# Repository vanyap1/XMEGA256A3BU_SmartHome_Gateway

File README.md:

# XMEGA256A3BU_SmartHome_Gateway

## Опис проекту
Це шлюз для розумного будинку, який може з'єднувати різні типи пристроїв з різними інтерфейсами, передавати та буферизувати між ними інформацію, реалізувати власну логіку та багато іншого.

## Можливості
- Підтримка інтерфейсів: LAN, CAN, SPI, I2C, GPIO
- Релейні виходи та входи з оптичною розв'язкою
- SD карта для логів
- Веб сервер для керування

## Структура проекту
- **XMEGA_A3BU**: Основний код проекту
  - `main.c`: Головний файл програми
  - `driver/`: Драйвери для різних периферійних пристроїв
  - `libs/`: Бібліотеки для роботи з різними інтерфейсами та пристроями
- **eagle_src**: Схеми та плати проекту
  - `controller_V1.brd`: Файл плати
  - `controller_V1.sch`: Схема проекту

## Контролер
В проекті використовується контролер **XMEGA256A3BU**. Основні переваги цього контролера:
- Висока продуктивність завдяки 8/16-бітному процесору
- Велика кількість периферійних інтерфейсів
- Низьке енергоспоживання
- Вбудована підтримка USB

## Фото модуля

## Інструкції по збірці
Для збірки проекту використовуйте Makefile, який знаходиться у директорії `XMEGA_A3BU/Debug/`.

```sh
cd XMEGA_A3BU/Debug/
make

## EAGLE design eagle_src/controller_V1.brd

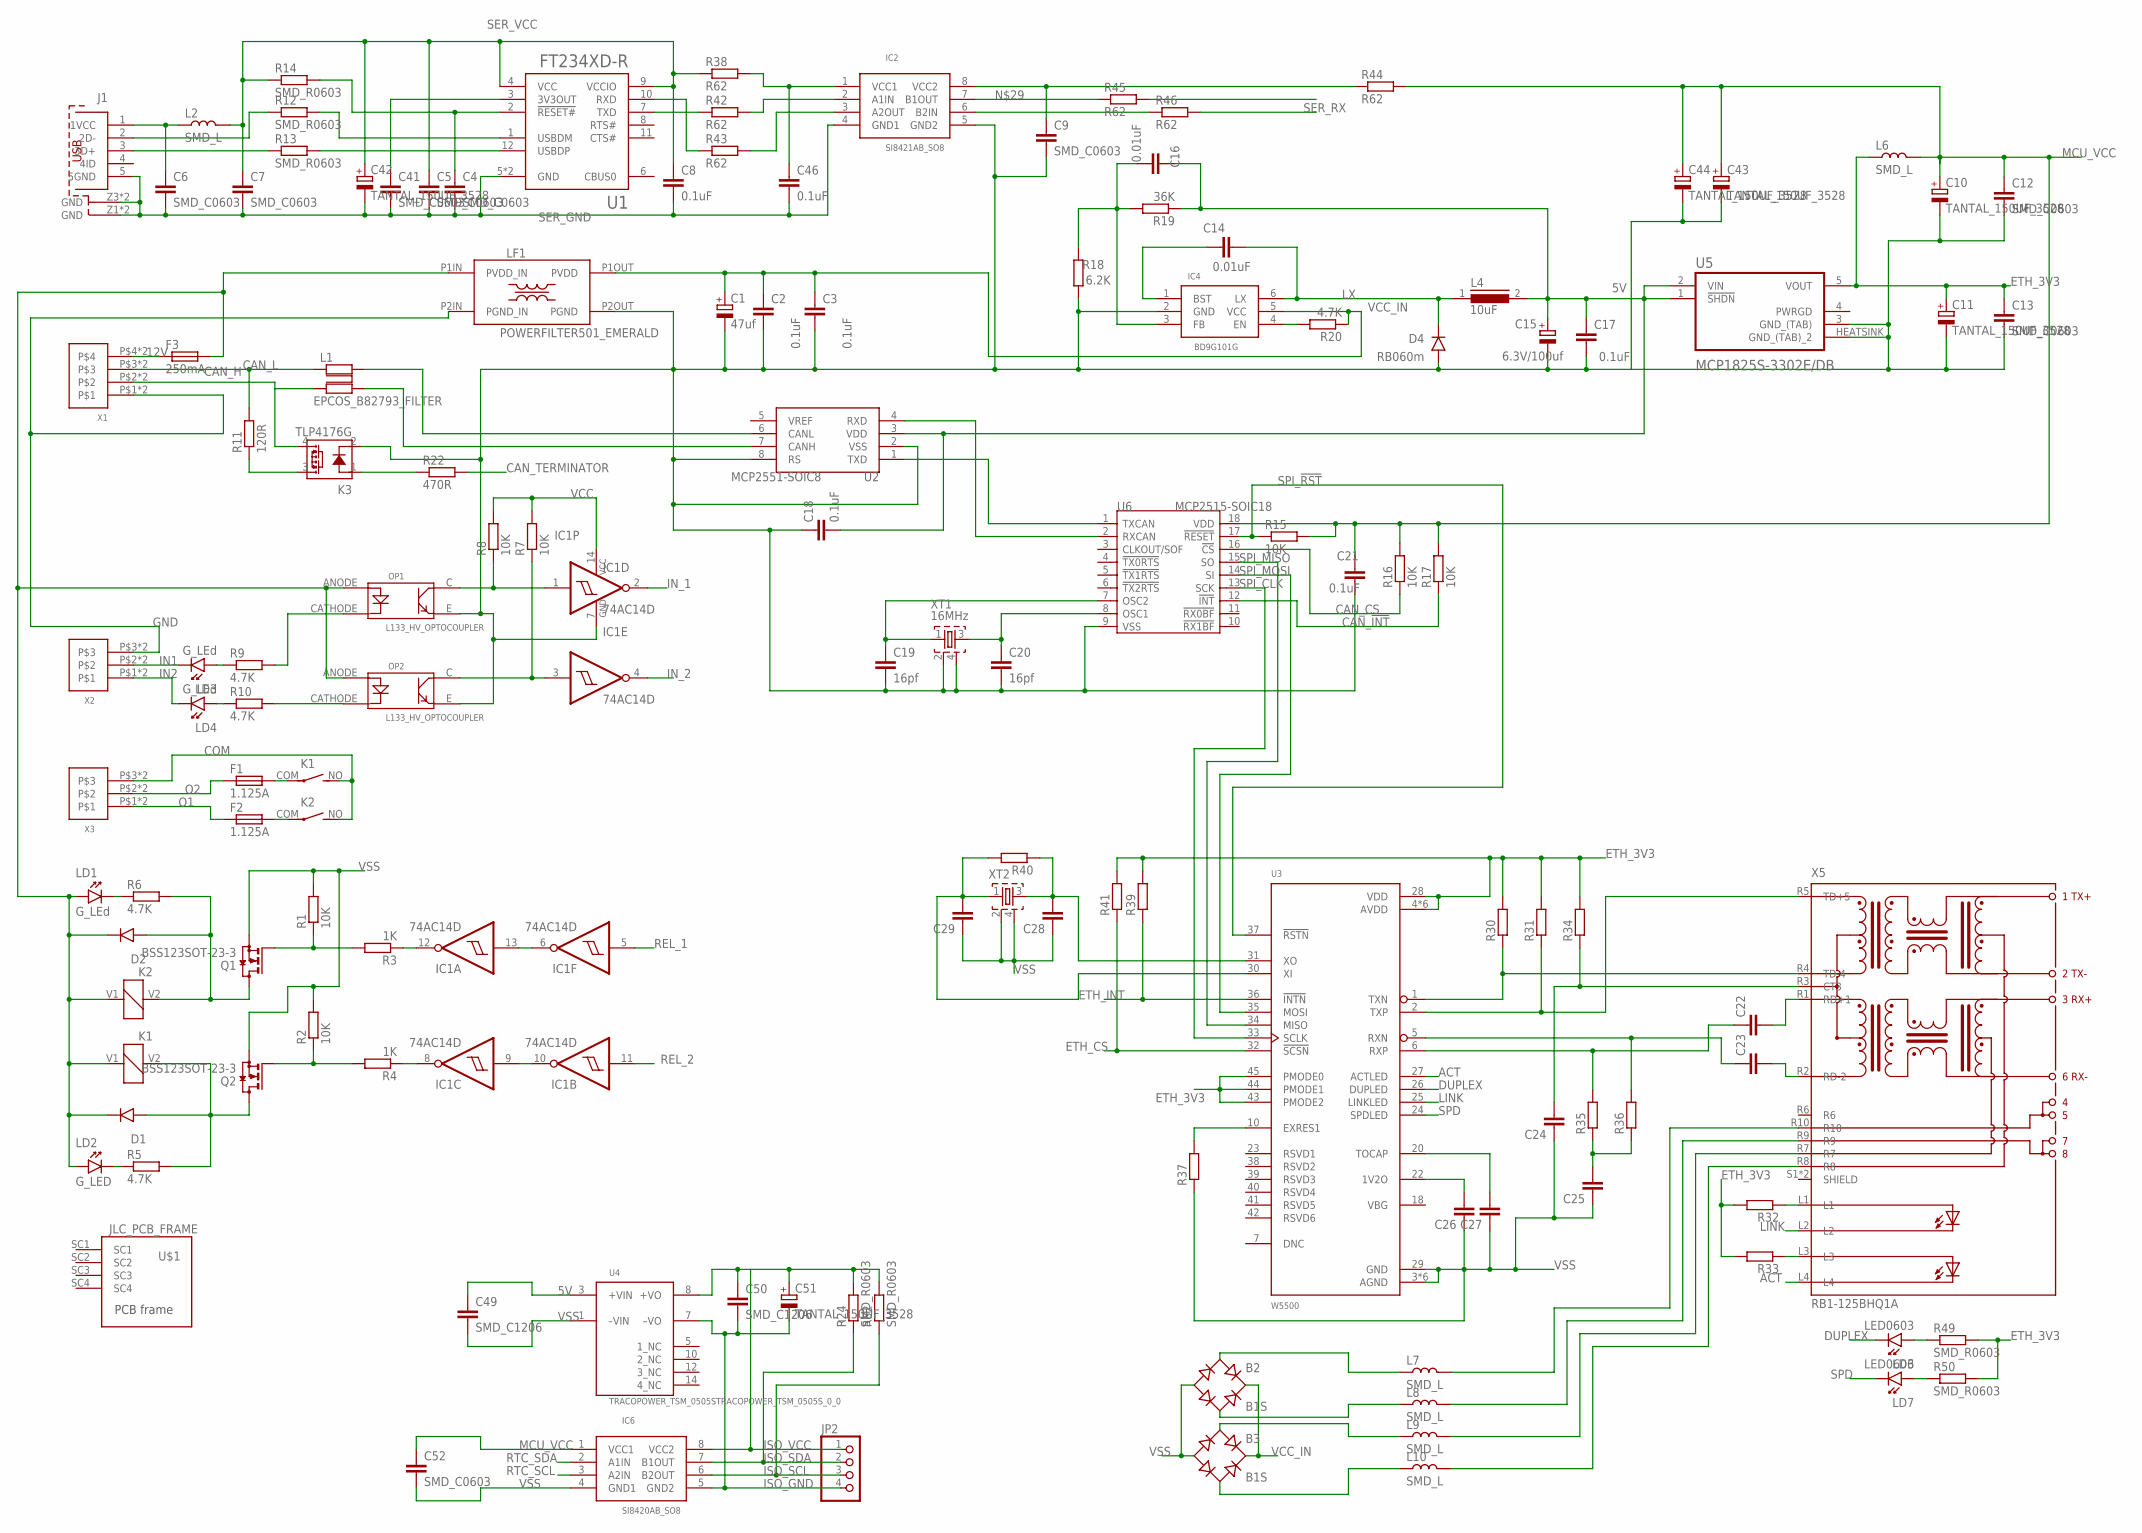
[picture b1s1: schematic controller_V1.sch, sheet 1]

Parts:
B2, B3: B1S; MBS
C1: 47uf; 5.08MM
C2, C3: 0.1uF; 1206
C4, C5, C6, C7, C9, C12, C13, C22, C23, C26, C27, C28, C29, C41, C52: SMD_C0603; 0603
C8, C17, C18, C21, C46: 0.1uF; 0603
C10, C11, C42, C43, C44, C51: TANTAL_150UF_3528; KA-3528ASYC
C14, C16: 0.01uF; 0603
C15: 6.3V/100uf; D/7343-31R
C19, C20: 16pf; 0603
C24: 0.1uf; 0603
C25: 10nf; 0603
C49, C50: SMD_C1206; 1206
D1, D2: D_MBRA340G; SMA403D
D4: RB060m; SMA403D
F1, F2: 1.125A; FUSE_DIP_2.5A250V
F3: 250mA; SMD_2410_FUSE_NOK
IC1: 74AC14D; SO14
IC2: SI8421AB_SO8; SO8
IC4: BD9G101G; SOT-23(6)
IC6: SI8420AB_SO8; SO8
J1: MINI_USB_TYP_B_@; 65100516121
JP2: PINHD-1X4; 1X04
K1, K2: 12-H1(610); 12-H1(610)_DIP
K3: TLP4176G; SOP04
L1: EPCOS_B82793_FILTER; EPCOS_FILTER
L2, L6, L7, L8, L9, L10: SMD_L; 0805
L4: 10uF; DR74
LD1, LD3, LD4: G_LEd; 3MM_DIP_LED
LD2: G_LED; 3MM_DIP_LED
LD6, LD7: LED0603; 0603_P
LF1: POWERFILTER501_EMERALD; POWERFILTER
OP1, OP2: L133_HV_OPTOCOUPLER; HV_OPTOCOUPLER_L133
Q1, Q2: BSS123SOT-23-3; SOT-23(3)
R1, R2, R7, R8, R15, R16, R17: 10K; 0603
R3, R4: 1K; 0603
R5, R6, R9, R10, R20: 4.7K; 0603
R11: 120R; VMTA55
R12, R13, R14, R24, R30, R31, R32, R33, R34, R35, R36, R37, R39, R40, R41, R49, R50, R52: SMD_R0603; 0603
R18: 6.2K; 0603
R19: 36K; 0603
R22: 470R; 0603
R38, R42, R43, R44, R45, R46: R62; 0603
U1: FT234XD-R; IC_FT234XD-R
U2: MCP2551-SOIC8; SO8
U3: W5500; QFP50P900X900X160-48N
U4: TRACOPOWER_TSM_0505STRACOPOWER_TSM_0505S_0_0; TRACOPOWER_TSM_0505S_0
U5: MCP1825S-3302E/DB; SOT230P700X180-4N
U6: MCP2515-SOIC18; SO18L
U$1: JLC_PCB_FRAME; 80X100_PCB_FRAME
X1: WAGO250_X4; WAGO250_FP_4X
X2, X3: WAGO250_X3; WAGO250_FP_3X
X5: RB1-125BHQ1A
XT1: 16MHz; QUARTZ_3X3MM
XT2: QUARTZ_ZQ; QUARTZ_3X3MM

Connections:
5V: C15.+, C16.2, C17.2, C18.2, C49.1, L4.2, R19.1, U2.3 (VDD), U4.3 (+VIN), U5.1 (!SHDN), U5.2 (VIN)
12V: F3.P$1 (1), X1.P$4, X1.U$4
ACT: U3.27 (ACTLED), X5.L4
CAN_!INT: R17.1, U6.12 (!INT); also elsewhere on the board
CAN_CS: R16.1, U6.16 (!CS); also elsewhere on the board
CAN_H: K3.4 (DS2), L1.P$2 (2), X1.P$2, X1.U$2
CAN_L: L1.P$1 (1), R11.2, X1.P$3, X1.U$3
CAN_TERMINATOR: R22.2; also elsewhere on the board
COM: K1.NO (S), K2.NO (S), X3.P$3, X3.U$3
DUPLEX: LD6.1 (K), U3.26 (DUPLED)
ETH_3V3: C11.P (+), C13.1, L6.1, R30.2, R31.2, R32.2, R33.2, R34.2, R39.2, R41.2, R49.2, R50.2, U3.4 (AVDD), U3.8 (AVDD), U3.11 (AVDD), U3.15 (AVDD), U3.17 (AVDD), U3.21 (AVDD), U3.28 (VDD), U3.43 (PMODE2), U3.44 (PMODE1), U3.45 (PMODE0), U5.5 (VOUT)
ETH_CS: R41.1, U3.32 (!SCSN); also elsewhere on the board
ETH_INT: R39.1, U3.36 (!INTN); also elsewhere on the board
GND: LF1.P2IN (PGND_IN), X1.P$1, X1.U$1, X2.P$3, X2.U$3
IN1: LD3.K, X2.P$2, X2.U$2
IN2: LD4.K, X2.P$1, X2.U$1
IN_1: IC1.2 (O); also elsewhere on the board
IN_2: IC1.4 (O); also elsewhere on the board
ISO_GND: C50.2, C51.M (-), IC6.5 (GND2), JP2.4, U4.7 (–VO)
ISO_SCL: IC6.6 (B2OUT), JP2.3, R52.1
ISO_SDA: IC6.7 (B1OUT), JP2.2, R24.1
ISO_VCC: C50.1, C51.P (+), IC6.8 (VCC2), JP2.1, R24.2, R52.2, U4.8 (+VO)
LINK: U3.25 (LINKLED), X5.L2
LX: C14.2, D4.P$1 (C), IC4.6 (LX), L4.1
MCU_VCC: C10.P (+), C12.1, C21.1, C43.P (+), C44.P (+), C52.1, IC6.1 (VCC1), L6.2, R15.2, R16.2, R17.2, R44.2, U6.18 (VDD); also elsewhere on the board
unnamed: IC2.3 (A2OUT), R43.2
unnamed: F1.P$2 (2), K1.COM
unnamed: F2.P$2 (2), K2.COM
unnamed: C41.1, U1.3 (3V3OUT)
unnamed: Q2.1 (G), R2.1, R4.2
unnamed: D1.P$2 (A), K1.V2 (2), Q2.3 (D), R5.2
unnamed: D2.P$2 (A), K2.V2 (2), Q1.3 (D), R6.2
unnamed: Q1.1 (G), R1.1, R3.2
unnamed: LD1.K, R6.1
unnamed: LD2.K, R5.1
unnamed: IC2.2 (A1IN), R42.2
unnamed: IC1.9 (I), IC1.10 (O)
unnamed: IC1.8 (O), R4.1
unnamed: IC1.6 (O), IC1.13 (I)
unnamed: IC1.12 (O), R3.1
unnamed: IC1.1 (I), OP1.C (COLLECTOR), R8.1
unnamed: IC1.3 (I), OP2.C (COLLECTOR), R7.1
unnamed: L10.2, X5.R8
unnamed: C46.1, IC2.1 (VCC1), R38.2
unnamed: D1.P$1 (C), D2.P$1 (C), F3.P$2 (2), K1.V1 (1), K2.V1 (1), LD1.A, LD2.A, LF1.P1IN (PVDD_IN), OP1.ANODE (ANOD), OP2.ANODE (ANOD)
unnamed: OP2.CATHODE (CATHOD), R10.2
unnamed: OP1.CATHODE (CATHOD), R9.2
unnamed: LD3.A, R9.1
unnamed: LD4.A, R10.1
unnamed: C9.1, IC2.8 (VCC2), R44.1
unnamed: IC2.7 (B1OUT), R45.1
unnamed: IC2.6 (B2IN), R46.1
unnamed: K3.3 (DS1), R11.1
unnamed: U2.1 (TXD), U6.1 (TXCAN)
unnamed: J1.3 (3D+), R13.1
unnamed: U2.4 (RXD), U6.2 (RXCAN)
unnamed: R13.2, U1.12 (USBDP)
unnamed: R12.2, U1.1 (USBDM)
unnamed: J1.2 (2D-), R12.1
unnamed: C4.1, R14.2, U1.2 (!RESET#)
unnamed: R42.1, U1.7 (TXD)
unnamed: C6.1, J1.1 (1VCC), L2.1
unnamed: L9.2, X5.R7
unnamed: L8.2, X5.R9
unnamed: R43.1, U1.10 (RXD)
unnamed: L1.P$3 (3), U2.7 (CANH)
unnamed: L1.P$4 (4), U2.6 (CANL)
unnamed: C14.1, IC4.1 (BST)
unnamed: L7.2, X5.R10
unnamed: C16.1, IC4.3 (FB), R18.2, R19.2
unnamed: IC4.4 (EN), R20.2
unnamed: C19.1, U6.7 (OSC2), XT1.1
unnamed: K3.1 (A), R22.1
unnamed: C20.1, U6.8 (OSC1), XT1.3
unnamed: B2.AC1, L7.1
unnamed: B2.AC2, L8.1
unnamed: B3.AC1, L9.1
unnamed: B3.AC2, L10.1
unnamed: LD6.2 (A), R49.1
unnamed: LD7.2 (A), R50.1
unnamed: C22.1, R35.2, U3.6 (RXP)
unnamed: C23.1, R36.2, U3.5 (RXN)
unnamed: R30.1, U3.1 (TXN), X5.R4 (TD-4)
unnamed: R31.1, U3.2 (TXP), X5.R5 (TD+5)
unnamed: C24.2, R34.1, X5.R3 (CT3)
unnamed: C25.2, R35.1, R36.1
unnamed: C22.2, X5.R1 (RD+1)
unnamed: C23.2, X5.R2 (RD-2)
unnamed: R32.1, X5.L1
unnamed: R33.1, X5.L3
unnamed: C26.2, U3.22 (1V2O)
unnamed: C27.2, U3.20 (TOCAP)
unnamed: R37.2, U3.10 (EXRES1)
unnamed: C29.2, R40.2, U3.30 (XI), XT2.1
unnamed: C28.2, R40.1, U3.31 (XO), XT2.3
O1: F2.P$1 (1), X3.P$1, X3.U$1
O2: F1.P$1 (1), X3.P$2, X3.U$2
REL_1: IC1.5 (I); also elsewhere on the board
REL_2: IC1.11 (I); also elsewhere on the board
RTC_SCL: IC6.3 (A2IN); also elsewhere on the board
RTC_SDA: IC6.2 (A1IN); also elsewhere on the board
SER_GND: C4.2, C5.2, C6.2, C7.2, C8.2, C41.2, C42.M (-), C46.2, IC2.4 (GND1), J1.5 (5GND), J1.Z1 (GND), J1.Z2 (GND), J1.Z3 (GND), J1.Z4 (GND), U1.5 (GND), U1.13 (GND)
SER_RX: R46.2; also elsewhere on the board
SER_TX: R45.2; also elsewhere on the board
SER_VCC: C5.1, C7.1, C8.1, C42.P (+), L2.2, R14.1, R38.1, U1.4 (VCC), U1.9 (VCCIO)
SPD: LD7.1 (K), U3.24 (SPDLED)
SPI_!RST: R15.1, U3.37 (!RSTN), U6.17 (!RESET); also elsewhere on the board
SPI_CLK: U3.33 (SCLK), U6.13 (SCK); also elsewhere on the board
SPI_MISO: U3.34 (MISO), U6.15 (SO); also elsewhere on the board
SPI_MOSI: U3.35 (MOSI), U6.14 (SI); also elsewhere on the board
VCC: IC1.14 (VCC), R7.2, R8.2; also elsewhere on the board
VCC_IN: B2.+, B3.+, C1.P$2 (+), C2.1, C3.1, IC4.5 (VCC), LF1.P1OUT (PVDD), R20.1
VSS: B2.-, B3.-, C1.P$1 (-), C2.2, C3.2, C9.2, C10.M (-), C11.M (-), C12.2, C13.2, C15.-, C17.1, C18.1, C19.2, C20.2, C21.2, C24.1, C25.1, C26.1, C27.1, C28.1, C29.1, C43.M (-), C44.M (-), C49.2, C52.2, D4.P$2 (A), IC1.7 (GND), IC2.5 (GND2), IC4.2 (GND), IC6.4 (GND1), K3.2 (K), LF1.P2OUT (PGND), OP1.E (EMITTER), OP2.E (EMITTER), Q1.2 (S), Q2.2 (S), R1.2, R2.2, R18.1, R37.1, U2.2 (VSS), U2.8 (RS), U3.3 (AGND), U3.9 (AGND), U3.14 (AGND), U3.16 (AGND), U3.19 (AGND), U3.29 (GND), U3.48 (AGND), U4.1 (–VIN), U5.3 (GND_(TAB)), U5.HEATSINK (GND_(TAB)_2), U6.9 (VSS), XT1.2, XT1.4, XT2.2, XT2.4; also elsewhere on the board

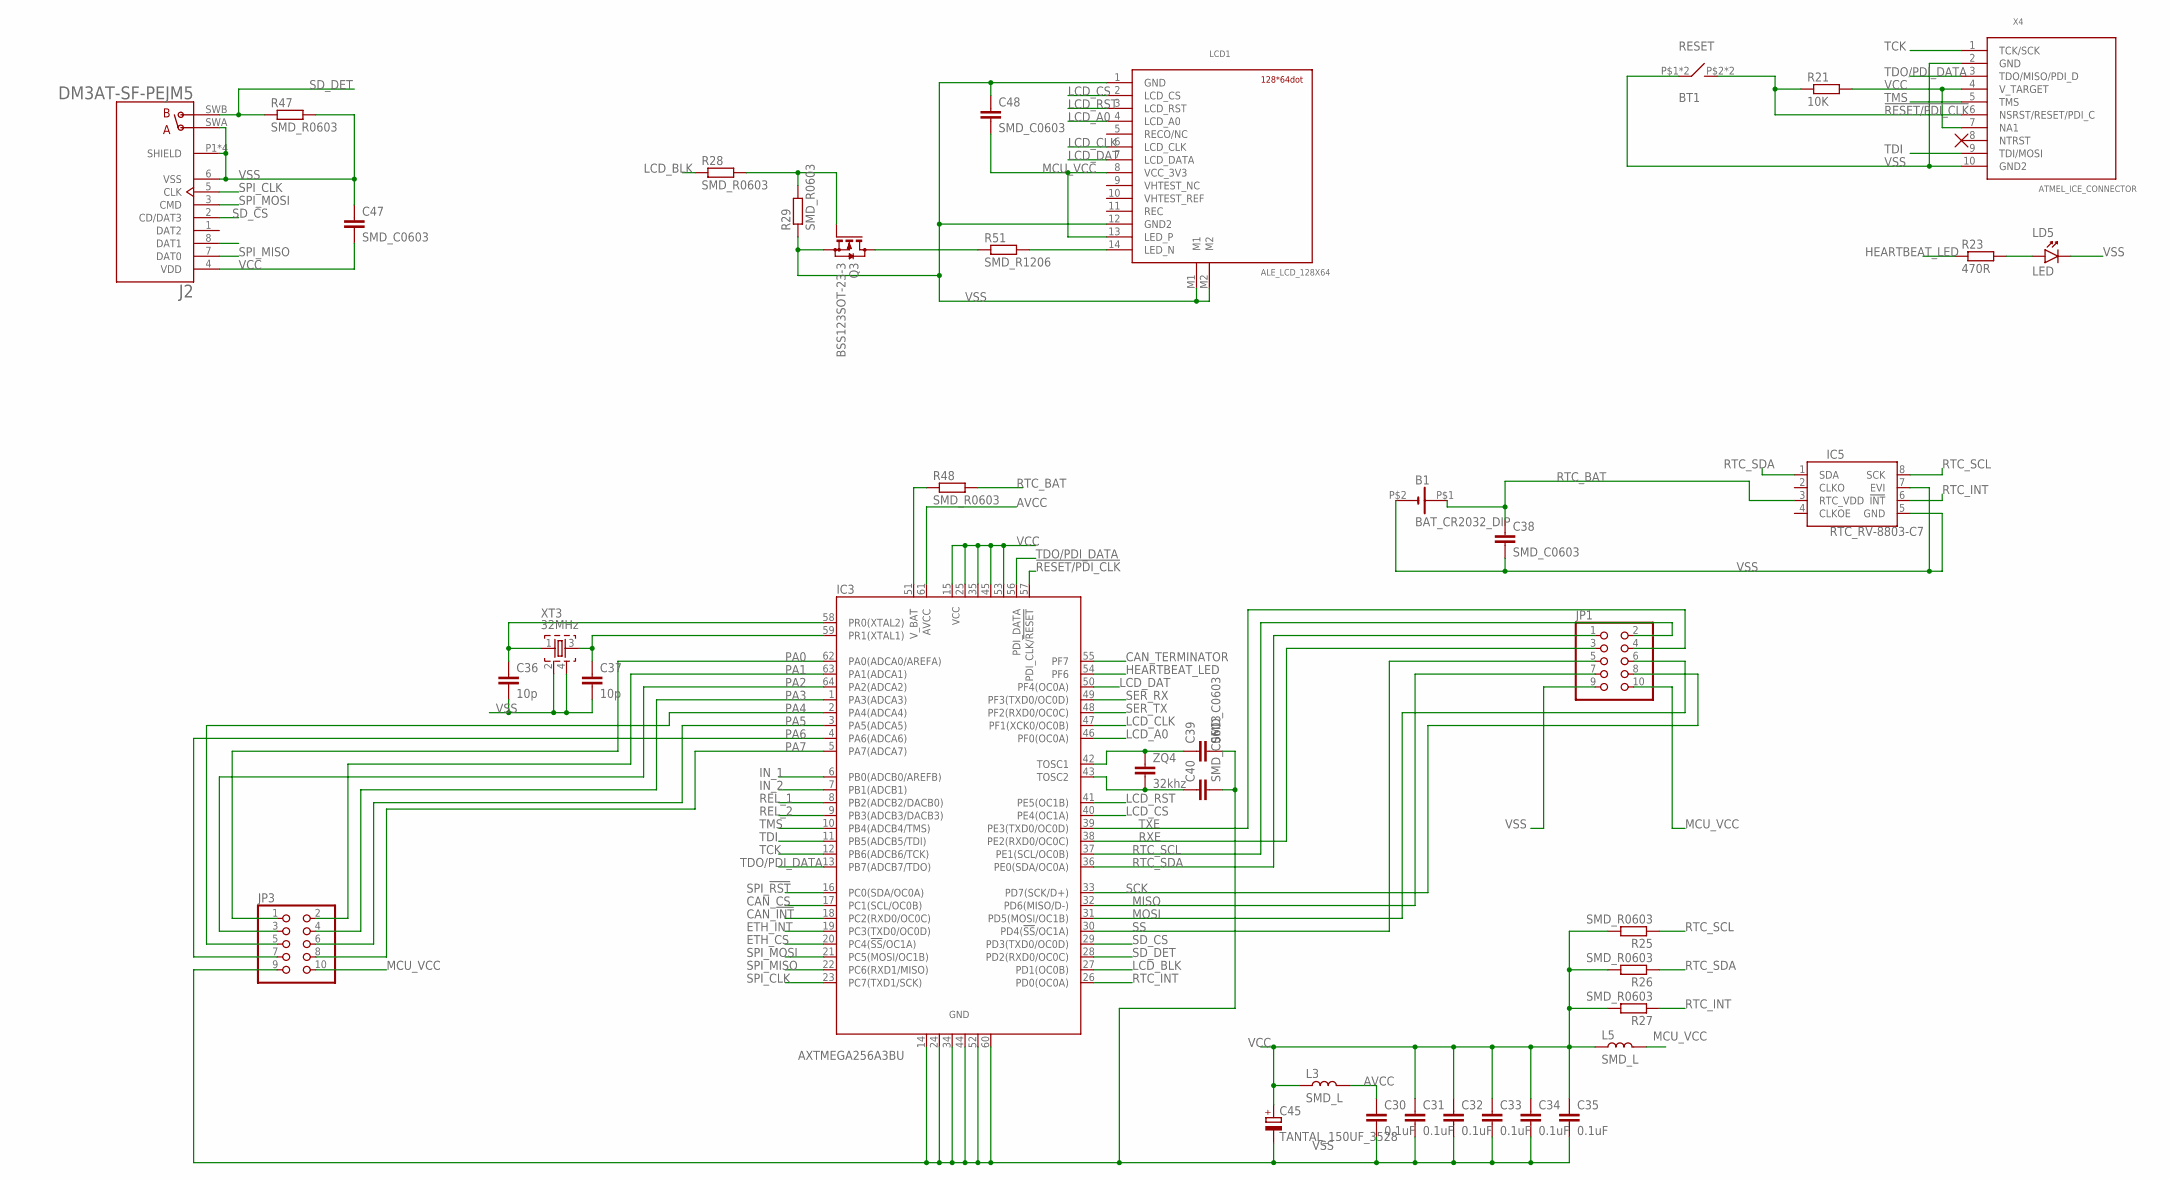
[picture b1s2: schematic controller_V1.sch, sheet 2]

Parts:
B1: BAT_CR2032_DIP; CR2032_DIP
BT1: RESET; 5X5MM_SMD_CY
C30, C31, C32, C33, C34, C35: 0.1uF; 0603
C36, C37: 10p; 0603
C38, C39, C40, C47, C48: SMD_C0603; 0603
C45: TANTAL_150UF_3528; KA-3528ASYC
IC3: AXTMEGA256A3BU; TQFP64
IC5: RTC_RV-8803-C7; C7_RTC
J2: DM3AT-SF-PEJM5; HRS_DM3AT-SF-PEJM5
JP1, JP3: PINHD-2X5; 2X05
L3, L5: SMD_L; 0805
LCD1: ALE_LCD_128X64; ALE_LCD_14PIN_CONNECTOR
LD5: LED; 3MM_DIP_LED
Q3: BSS123SOT-23-3; SOT-23(3)
R21: 10K; 0603
R23: 470R; 0603
R25, R26, R27, R28, R29, R47, R48: SMD_R0603; 0603
R51: SMD_R1206; 1206
X4: ATMEL_ICE_CONNECTOR; MINI10P_SPI/JTAG/PDI
XT3: 32MHz; QUARTZ_3X3MM
ZQ4: 32khz; 1206

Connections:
!RESET/PDI_CLK: BT1.P$2 (4), BT1.P$3 (4), IC3.57 (PDI_CLK/!RESET!), R21.1, X4.6 (NSRST/RESET/PDI_C)
AVCC: C30.1, IC3.61 (AVCC), L3.2
CAN_!INT: IC3.18 (PC2(RXD0/OC0C)); also elsewhere on the board
CAN_CS: IC3.17 (PC1(SCL/OC0B)); also elsewhere on the board
CAN_TERMINATOR: IC3.55 (PF7); also elsewhere on the board
ETH_CS: IC3.20 (PC4(!SS!/OC1A)); also elsewhere on the board
ETH_INT: IC3.19 (PC3(TXD0/OC0D)); also elsewhere on the board
HEARTBEAT_LED: IC3.54 (PF6), R23.1
IN_1: IC3.6 (PB0(ADCB0/AREFB)); also elsewhere on the board
IN_2: IC3.7 (PB1(ADCB1)); also elsewhere on the board
LCD_A0: IC3.46 (PF0(OC0A)), LCD1.4 (LCD_A0)
LCD_BLK: IC3.27 (PD1(OC0B)), R28.1
LCD_CLK: IC3.47 (PF1(XCK0/OC0B)), LCD1.6 (LCD_CLK)
LCD_CS: IC3.40 (PE4(OC1A)), LCD1.2 (LCD_CS)
LCD_DAT: IC3.50 (PF4(OC0A)), LCD1.7 (LCD_DATA)
LCD_RST: IC3.41 (PE5(OC1B)), LCD1.3 (LCD_RST)
MCU_VCC: C48.2, JP1.10, JP3.10, L5.2, LCD1.8 (VCC_3V3), LCD1.13 (LED_P); also elsewhere on the board
MISO: IC3.32 (PD6(MISO/D-)), JP1.7
MOSI: IC3.31 (PD5(MOSI/OC1B)), JP1.6
unnamed: C36.1, IC3.58 (PR0(XTAL2)), XT3.1
unnamed: C37.1, IC3.59 (PR1(XTAL1)), XT3.3
unnamed: LD5.A, R23.2
unnamed: IC3.51 (V_BAT), R48.1
unnamed: Q3.3 (D), R51.1
unnamed: LCD1.14 (LED_N), R51.2
unnamed: C40.1, IC3.43 (TOSC2), ZQ4.2
unnamed: C39.1, IC3.42 (TOSC1), ZQ4.1
unnamed: Q3.1 (G), R28.2, R29.2
PA0: IC3.62 (PA0(ADCA0/AREFA)), JP3.1
PA1: IC3.63 (PA1(ADCA1)), JP3.2
PA2: IC3.64 (PA2(ADCA2)), JP3.3
PA3: IC3.1 (PA3(ADCA3)), JP3.4
PA4: IC3.2 (PA4(ADCA4)), JP3.5
PA5: IC3.3 (PA5(ADCA5)), JP3.6
PA6: IC3.4 (PA6(ADCA6)), JP3.7
PA7: IC3.5 (PA7(ADCA7)), JP3.8
REL_1: IC3.8 (PB2(ADCB2/DACB0)); also elsewhere on the board
REL_2: IC3.9 (PB3(ADCB3/DACB3)); also elsewhere on the board
RTC_BAT: B1.P$1 (+), C38.1, IC5.3 (RTC_VDD), R48.2
RTC_INT: IC3.26 (PD0(OC0A)), IC5.6 (!INT), R27.1
RTC_SCL: IC3.37 (PE1(SCL/OC0B)), IC5.8 (SCK), JP1.2, R25.1; also elsewhere on the board
RTC_SDA: IC3.36 (PE0(SDA/OC0A)), IC5.1 (SDA), JP1.1, R26.1; also elsewhere on the board
RXE: IC3.38 (PE2(RXD0/OC0C)), JP1.3
SCK: IC3.33 (PD7(SCK/D+)), JP1.8
SD_CS: IC3.29 (PD3(TXD0/OC0D)), J2.2 (CD/DAT3)
SD_DET: IC3.28 (PD2(RXD0/OC0C)), J2.SWB (B), R47.1
SER_RX: IC3.49 (PF3(TXD0/OC0D)); also elsewhere on the board
SER_TX: IC3.48 (PF2(RXD0/OC0C)); also elsewhere on the board
SPI_!RST: IC3.16 (PC0(SDA/OC0A)); also elsewhere on the board
SPI_CLK: IC3.23 (PC7(TXD1/SCK)), J2.5 (CLK); also elsewhere on the board
SPI_MISO: IC3.22 (PC6(RXD1/MISO)), J2.7 (DAT0); also elsewhere on the board
SPI_MOSI: IC3.21 (PC5(MOSI/OC1B)), J2.3 (CMD); also elsewhere on the board
SS: IC3.30 (PD4(!SS!/OC1A)), JP1.5
TCK: IC3.12 (PB6(ADCB6/TCK)), X4.1 (TCK/SCK)
TDI: IC3.11 (PB5(ADCB5/TDI)), X4.9 (TDI/MOSI)
TDO/PDI_DATA: IC3.13 (PB7(ADCB7/TDO)), IC3.56 (PDI_DATA), X4.3 (TDO/MISO/PDI_D)
TMS: IC3.10 (PB4(ADCB4/TMS)), X4.5 (TMS)
TXE: IC3.39 (PE3(TXD0/OC0D)), JP1.4
VCC: C31.1, C32.1, C33.1, C34.1, C35.1, C45.P (+), C47.2, IC3.15 (VCC1), IC3.25 (VCC2), IC3.35 (VCC3), IC3.45 (VCC4), IC3.53 (VCC5), J2.4 (VDD), L3.1, L5.1, R21.2, R25.2, R26.2, R27.2, X4.4 (V_TARGET), X4.7 (NA1); also elsewhere on the board
VSS: B1.P$2 (-), BT1.P$1 (1), BT1.P$4 (1), C30.2, C31.2, C32.2, C33.2, C34.2, C35.2, C36.2, C37.2, C38.2, C39.2, C40.2, C45.M (-), C47.1, C48.1, IC3.14 (GND1), IC3.24 (GND2), IC3.34 (GND3), IC3.44 (GND4), IC3.52 (GND5), IC3.60 (GND6), IC5.5 (GND), IC5.7 (EVI), J2.6 (VSS), J2.P1 (SHIELD), J2.P2 (SHIELD), J2.P3 (SHIELD), J2.P4 (SHIELD), J2.SWA (A), JP1.9, JP3.9, LCD1.1 (GND), LCD1.12 (GND2), LCD1.M1, LCD1.M2, LD5.K, Q3.2 (S), R29.1, R47.2, X4.2 (GND), X4.10 (GND2), XT3.2, XT3.4; also elsewhere on the board

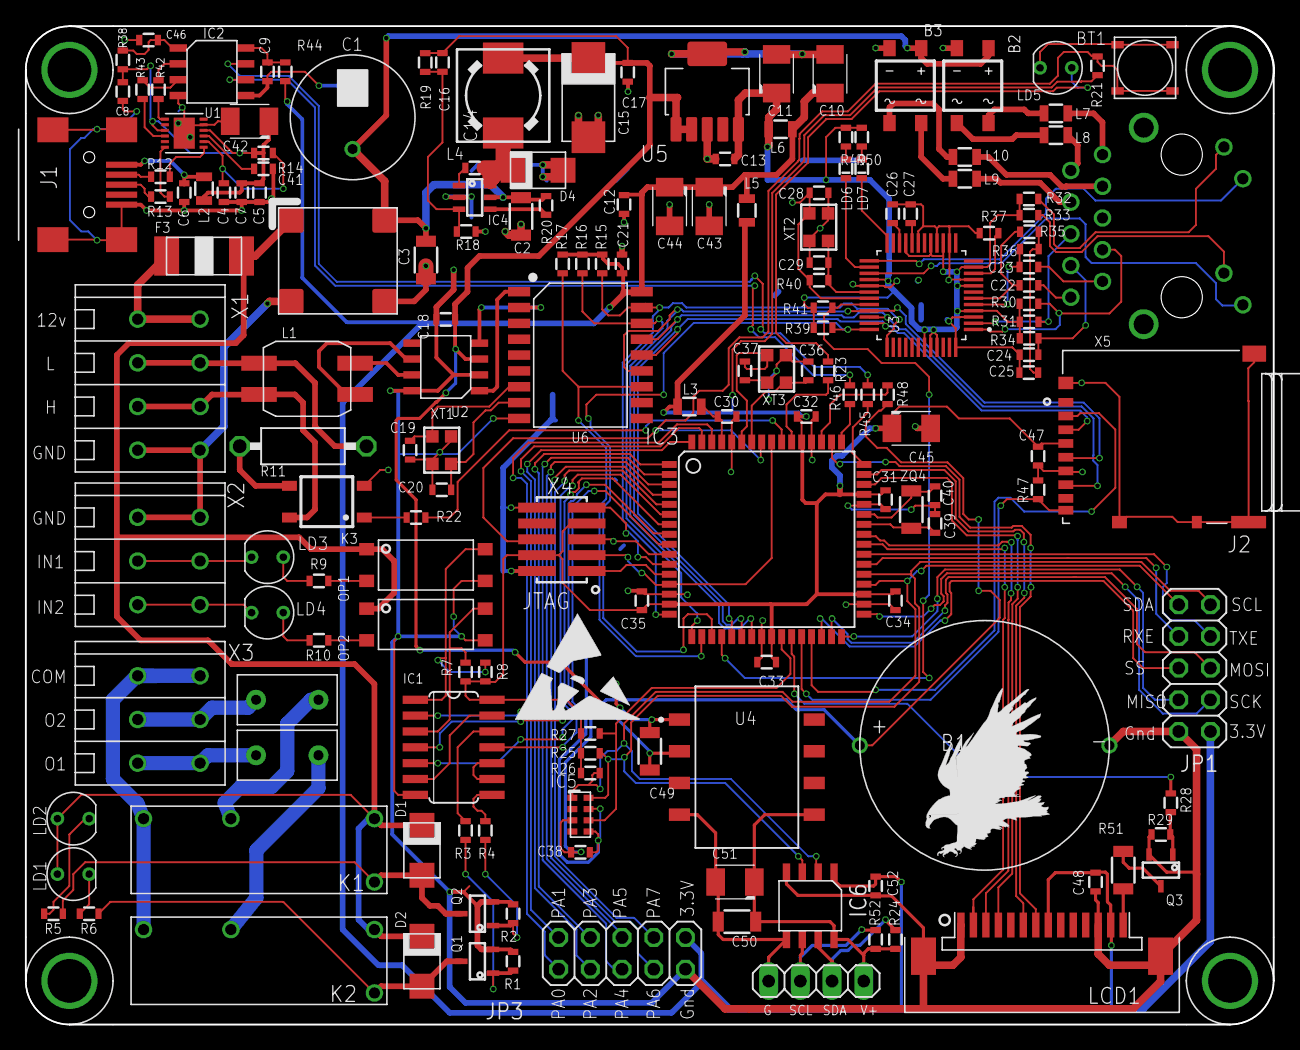
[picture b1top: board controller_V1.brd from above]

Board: 2 copper layers, 100.0 x 80.0 mm, 171 parts (1 on the bottom side), 153 nets.

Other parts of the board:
U$2, U$4: EAGLE-PLC-10MM
U$3: ESD_10.00

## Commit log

2025-01-05 img updated
2025-01-05 removed stm32 parts of code
